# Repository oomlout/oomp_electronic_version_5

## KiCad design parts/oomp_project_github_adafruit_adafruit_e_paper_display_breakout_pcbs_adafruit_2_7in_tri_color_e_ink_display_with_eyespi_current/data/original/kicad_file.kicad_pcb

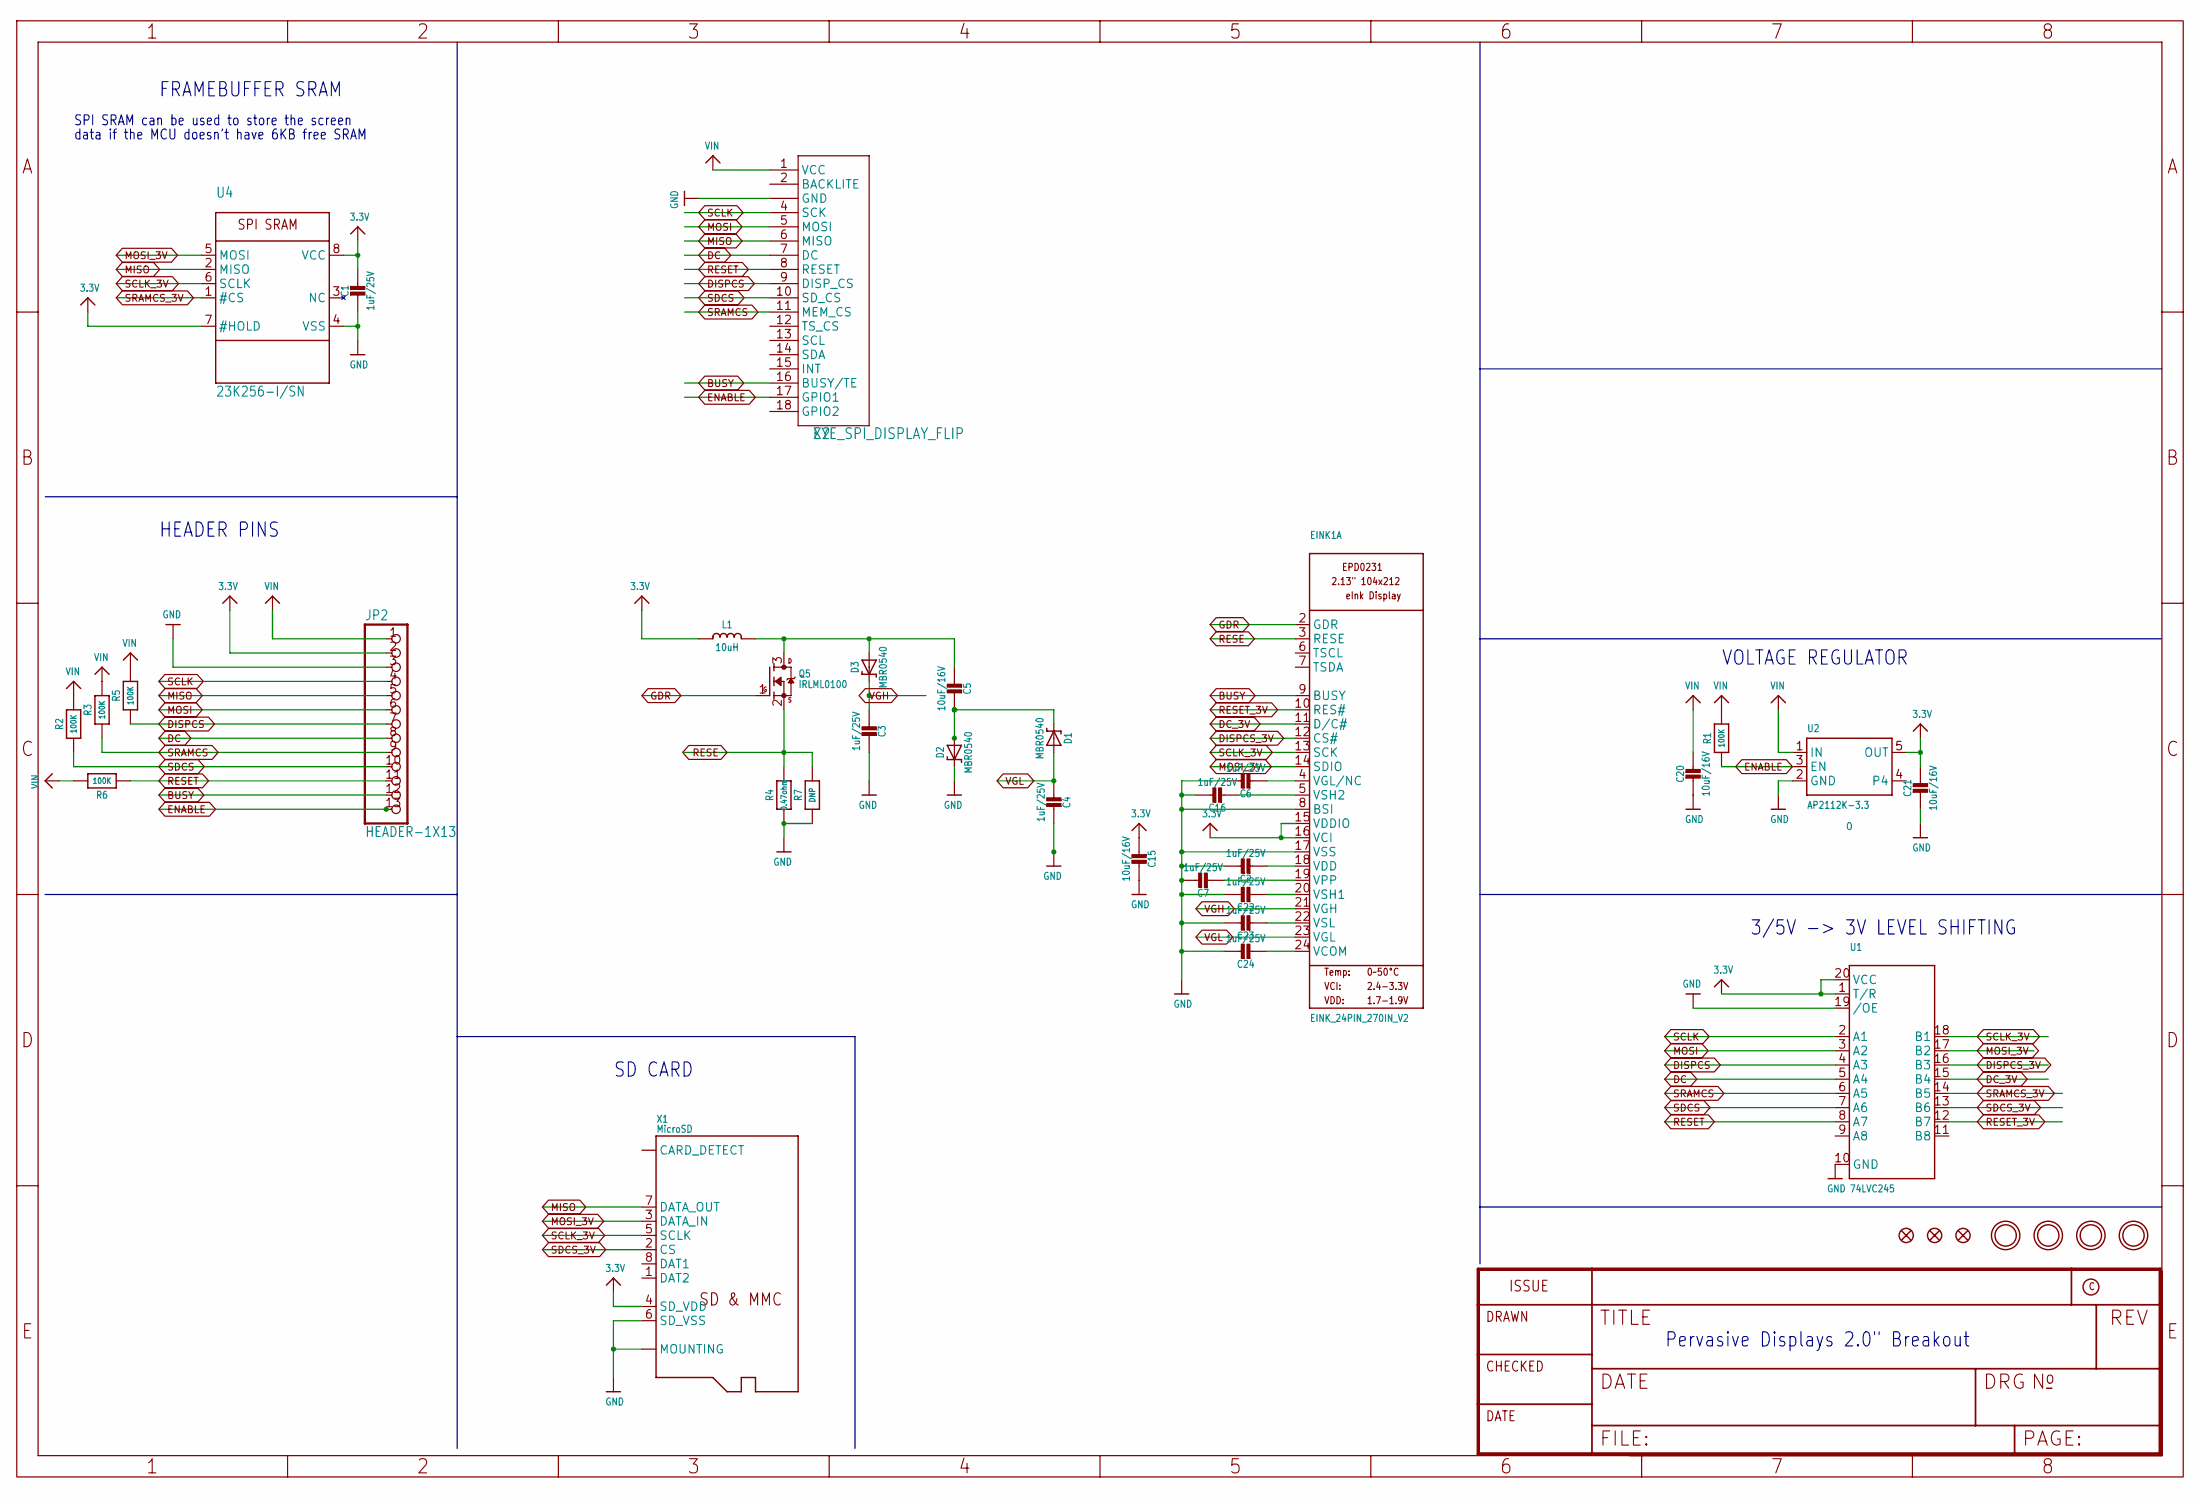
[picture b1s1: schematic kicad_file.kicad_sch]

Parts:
C1, C2, C3, C4, C6, C7, C16, C22, C23, C24: 1uF/25V; 0603-NO
C5, C15, C20, C21: 10uF/16V; 0805-NO
D1, D2, D3: MBR0540; SOD-123
EINK1: EINK_24PIN_270IN_V2; EINK_270IN_V2
FID1, FID2, FID3: FIDUCIAL_1MM
JP2: HEADER-1X13; 1X13_ROUND_70
L1: 10uH; INDUCTOR_4X4MM_NR401
Q5: IRLML0100; SOT23-WIDE
R1, R2, R3, R5, R6: 100K; 0603-NO
R4: 0.47ohm; 0603-NO
R7: DNP; 0603-NO
U1: 74LVC245; TSSOP20
U2: AP2112K-3.3; SOT23-5; JLC_ROTATION 0
U4: 23K256-I/SN; SOIC8_150MIL
U$3, U$4, U$5, U$6: MOUNTINGHOLE2.5; MOUNTINGHOLE_2.5_PLATED
X1: MicroSD; MICROSD; JLC_ROTATION 90
X2: EYE_SPI_DISPLAY_FLIP; EYE_SPI_DISPLAY_BOTCONTACT; LCSC C2856802

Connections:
3.3V: C1.1, C15.2, C21.1, EINK1.15 (VDDIO), EINK1.16 (VCI), JP2.2, L1.P$2 (2), U1.1 (T/R), U1.20 (VCC), U2.5 (OUT), U4.7 (#HOLD), U4.8 (VCC), X1.4 (SD_VDD)
BUSY: EINK1.9 (BUSY), JP2.12, X2.16 (BUSY/TE)
DC: JP2.8, U1.5 (A4), X2.7 (DC)
DC_3V: EINK1.11 (D/C#), U1.15 (B4)
DISPCS: JP2.7, R5.1, U1.4 (A3), X2.9 (DISP_CS)
DISPCS_3V: EINK1.12 (CS#), U1.16 (B3)
ENABLE: JP2.13, R1.1, U2.3 (EN), X2.17 (GPIO1)
GDR: EINK1.2 (GDR), Q5.1 (G)
GND: C1.2, C2.1, C3.2, C4.2, C6.1, C7.1, C15.1, C16.1, C20.2, C21.2, C22.1, C23.1, C24.1, D2.C, EINK1.8 (BSI), EINK1.17 (VSS), JP2.3, R4.2, R7.2, U1.10 (GND), U1.19 (/OE), U2.2 (GND), U4.4 (VSS), X1.6 (SD_VSS), X1.MT1 (MOUNTING), X1.MT2 (MOUNTING), X2.3 (GND), X2.SUPPORT1 (GND), X2.SUPPORT2 (GND)
MISO: JP2.5, U4.2 (MISO), X1.7 (DATA_OUT), X2.6 (MISO)
MOSI: JP2.6, U1.3 (A2), X2.5 (MOSI)
MOSI_3V: EINK1.14 (SDIO), U1.17 (B2), U4.5 (MOSI), X1.3 (DATA_IN)
unnamed: C7.2, EINK1.19 (VPP)
unnamed: C5.2, D1.C, D2.A
unnamed: C5.1, D3.A, L1.P$1 (1), Q5.3 (D)
unnamed: C16.2, EINK1.5 (VSH2)
unnamed: C2.2, EINK1.18 (VDD)
unnamed: C22.2, EINK1.20 (VSH1)
unnamed: C6.2, EINK1.4 (VGL/NC)
unnamed: C23.2, EINK1.22 (VSL)
unnamed: C24.2, EINK1.24 (VCOM)
RESE: EINK1.3 (RESE), Q5.2 (S), R4.1, R7.1
RESET: JP2.11, R6.1, U1.8 (A7), X2.8 (RESET)
RESET_3V: EINK1.10 (RES#), U1.12 (B7)
SCLK: JP2.4, U1.2 (A1), X2.4 (SCK)
SCLK_3V: EINK1.13 (SCK), U1.18 (B1), U4.6 (SCLK), X1.5 (SCLK)
SDCS: JP2.10, R2.1, U1.7 (A6), X2.10 (SD_CS)
SDCS_3V: U1.13 (B6), X1.2 (CS)
SRAMCS: JP2.9, R3.1, U1.6 (A5), X2.11 (MEM_CS)
SRAMCS_3V: U1.14 (B5), U4.1 (#CS)
VGH: C3.1, D3.C, EINK1.21 (VGH)
VGL: C4.1, D1.A, EINK1.23 (VGL)
VIN: C20.1, JP2.1, R1.2, R2.2, R3.2, R5.2, R6.2, U2.1 (IN), X2.1 (VCC)

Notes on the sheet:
SD CARD
Pervasive Displays 2.0" Breakout
VOLTAGE REGULATOR
3/5V -> 3V LEVEL SHIFTING
FRAMEBUFFER SRAM
data if the MCU doesn't have 6KB free SRAM
HEADER PINS
SPI SRAM can be used to store the screen

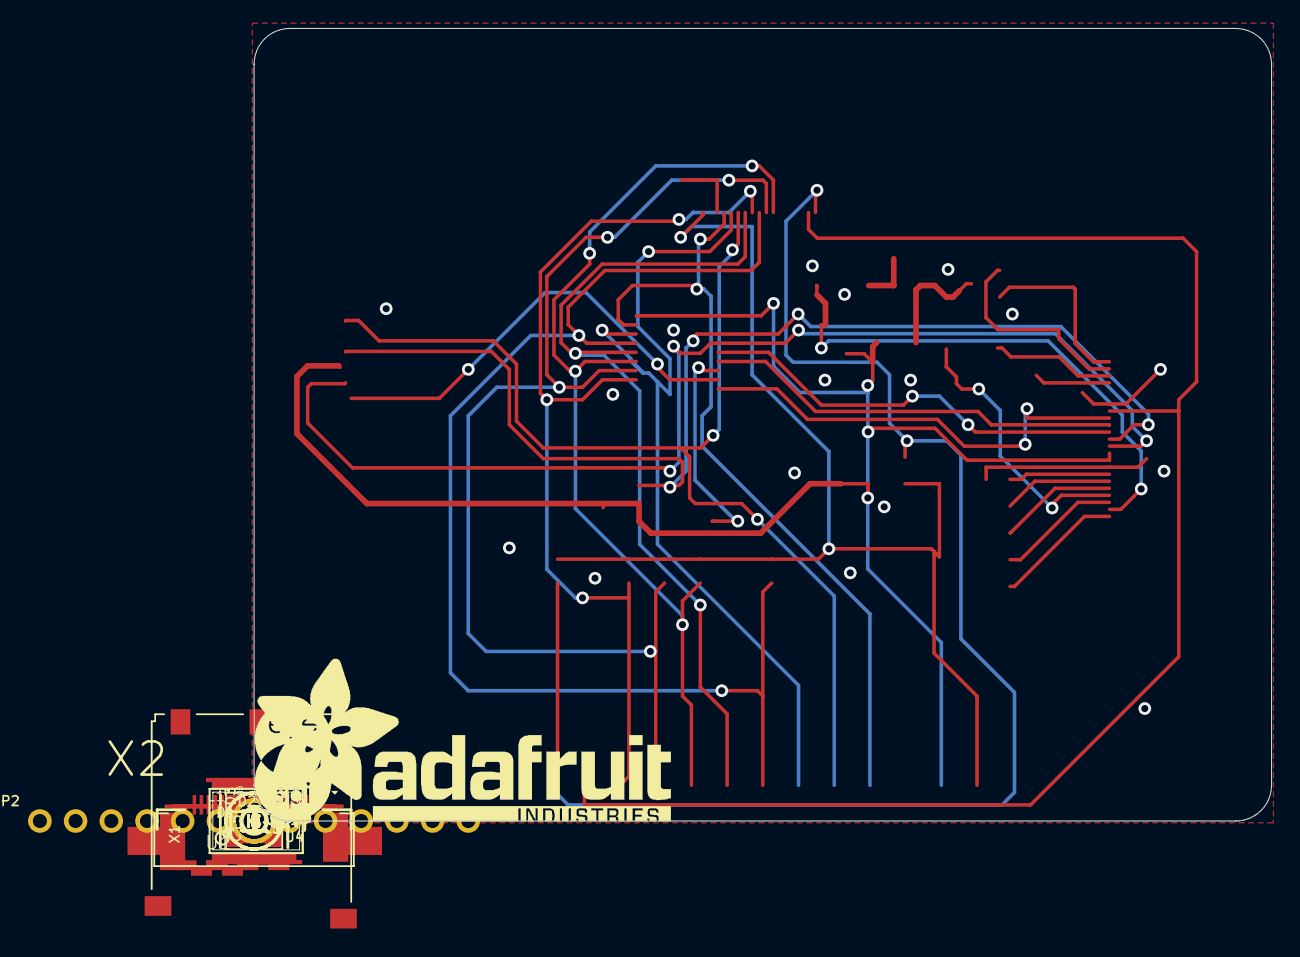
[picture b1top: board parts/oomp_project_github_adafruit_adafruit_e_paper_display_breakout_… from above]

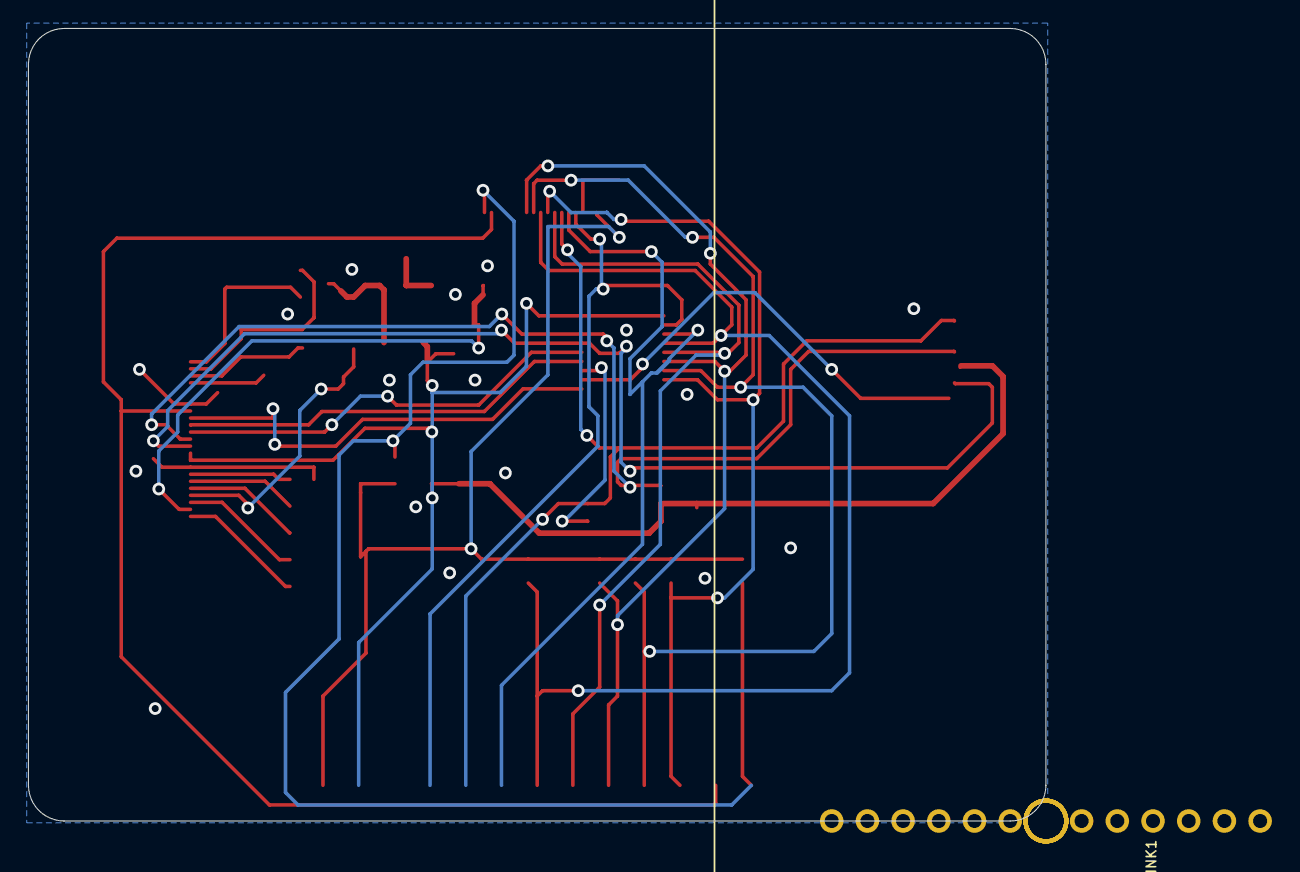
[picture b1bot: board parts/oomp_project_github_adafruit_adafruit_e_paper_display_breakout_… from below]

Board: 2 copper layers, 72.4 x 56.4 mm, 72 parts (15 on the bottom side), 33 nets.

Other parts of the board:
PLABEL0: PLABEL0
PLABEL1: PLABEL1
PLABEL2: PLABEL2
PLABEL3: PLABEL3
PLABEL4: PLABEL4
PLABEL5: PLABEL5
PLABEL6: PLABEL6
PLABEL7: PLABEL7
PLABEL8: PLABEL8
PLABEL9: PLABEL9
PLABEL10: PLABEL10
PLABEL11: PLABEL11
PLABEL12: PLABEL12
PLABEL13: PLABEL13
PLABEL14: PLABEL14
PLABEL15: PLABEL15
PLABEL16: PLABEL16
PLABEL17: PLABEL17
PLABEL18: PLABEL18
PLABEL19: PLABEL19
PLABEL20: PLABEL20
PLABEL21: PLABEL21
PLABEL22: PLABEL22
PLABEL23: PLABEL23
PLABEL24: PLABEL24
PLABEL25: PLABEL25
PLABEL26: PLABEL26
PLABEL27: PLABEL27
PLABEL28: PLABEL28
U$1: EYESPI_MINI_LOGO
U$9: PCBFEAT-REV-040
U$39: ADAFRUIT_TEXT_30MM

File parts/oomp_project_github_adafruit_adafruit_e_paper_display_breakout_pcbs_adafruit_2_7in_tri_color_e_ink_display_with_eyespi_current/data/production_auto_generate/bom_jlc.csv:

Comment,Designator,Footprint,LCSC Part #
,JP2,Adafruit 2.7in Tri-Color eInk Display with EYESPI-import-fps:1X13_ROUND_70,C2894936
,U$39,Adafruit 2.7in Tri-Color eInk Display with EYESPI-import-fps:ADAFRUIT_TEXT_30MM,
,U$1,Adafruit 2.7in Tri-Color eInk Display with EYESPI-import-fps:EYESPI_MINI_LOGO,
,U$9,Adafruit 2.7in Tri-Color eInk Display with EYESPI-import-fps:PCBFEAT-REV-040,
,PLABEL0,Adafruit 2.7in Tri-Color eInk Display with EYESPI-import-fps:PLABEL0,
,PLABEL1,Adafruit 2.7in Tri-Color eInk Display with EYESPI-import-fps:PLABEL1,
,PLABEL10,Adafruit 2.7in Tri-Color eInk Display with EYESPI-import-fps:PLABEL10,
,PLABEL11,Adafruit 2.7in Tri-Color eInk Display with EYESPI-import-fps:PLABEL11,
,PLABEL12,Adafruit 2.7in Tri-Color eInk Display with EYESPI-import-fps:PLABEL12,
,PLABEL13,Adafruit 2.7in Tri-Color eInk Display with EYESPI-import-fps:PLABEL13,
,PLABEL14,Adafruit 2.7in Tri-Color eInk Display with EYESPI-import-fps:PLABEL14,
,PLABEL15,Adafruit 2.7in Tri-Color eInk Display with EYESPI-import-fps:PLABEL15,
,PLABEL16,Adafruit 2.7in Tri-Color eInk Display with EYESPI-import-fps:PLABEL16,
,PLABEL17,Adafruit 2.7in Tri-Color eInk Display with EYESPI-import-fps:PLABEL17,
,PLABEL18,Adafruit 2.7in Tri-Color eInk Display with EYESPI-import-fps:PLABEL18,
,PLABEL19,Adafruit 2.7in Tri-Color eInk Display with EYESPI-import-fps:PLABEL19,
,PLABEL2,Adafruit 2.7in Tri-Color eInk Display with EYESPI-import-fps:PLABEL2,
,PLABEL20,Adafruit 2.7in Tri-Color eInk Display with EYESPI-import-fps:PLABEL20,
,PLABEL21,Adafruit 2.7in Tri-Color eInk Display with EYESPI-import-fps:PLABEL21,
,PLABEL22,Adafruit 2.7in Tri-Color eInk Display with EYESPI-import-fps:PLABEL22,
,PLABEL23,Adafruit 2.7in Tri-Color eInk Display with EYESPI-import-fps:PLABEL23,
,PLABEL24,Adafruit 2.7in Tri-Color eInk Display with EYESPI-import-fps:PLABEL24,
,PLABEL25,Adafruit 2.7in Tri-Color eInk Display with EYESPI-import-fps:PLABEL25,
,PLABEL26,Adafruit 2.7in Tri-Color eInk Display with EYESPI-import-fps:PLABEL26,
,PLABEL27,Adafruit 2.7in Tri-Color eInk Display with EYESPI-import-fps:PLABEL27,
,PLABEL28,Adafruit 2.7in Tri-Color eInk Display with EYESPI-import-fps:PLABEL28,
,PLABEL3,Adafruit 2.7in Tri-Color eInk Display with EYESPI-import-fps:PLABEL3,
,PLABEL4,Adafruit 2.7in Tri-Color eInk Display with EYESPI-import-fps:PLABEL4,
,PLABEL5,Adafruit 2.7in Tri-Color eInk Display with EYESPI-import-fps:PLABEL5,
,PLABEL6,Adafruit 2.7in Tri-Color eInk Display with EYESPI-import-fps:PLABEL6,
,PLABEL7,Adafruit 2.7in Tri-Color eInk Display with EYESPI-import-fps:PLABEL7,
,PLABEL8,Adafruit 2.7in Tri-Color eInk Display with EYESPI-import-fps:PLABEL8,
,PLABEL9,Adafruit 2.7in Tri-Color eInk Display with EYESPI-import-fps:PLABEL9,
0.47ohm,R4,Adafruit 2.7in Tri-Color eInk Display with EYESPI-import-fps:0603-NO,
100K,"R1,R2,R3,R5,R6",Adafruit 2.7in Tri-Color eInk Display with EYESPI-import-fps:0603-NO,C25803
10uF/16V,"C5,C15,C20,C21",Adafruit 2.7in Tri-Color eInk Display with EYESPI-import-fps:0805-NO,
10uH,L1,Adafruit 2.7in Tri-Color eInk Display with EYESPI-import-fps:INDUCTOR_4X4MM_NR401,
1uF/25V,"C1,C2,C3,C4,C6,C7,C16,C22,C23,C24",Adafruit 2.7in Tri-Color eInk Display with EYESPI-import-fps:0603-NO,C5673
23K256-I/SN,U4,Adafruit 2.7in Tri-Color eInk Display with EYESPI-import-fps:SOIC8_150MIL,
74LVC245,U1,Adafruit 2.7in Tri-Color eInk Display with EYESPI-import-fps:TSSOP20,
AP2112K-3.3,U2,Adafruit 2.7in Tri-Color eInk Display with EYESPI-import-fps:SOT23-5,
DNP,R7,Adafruit 2.7in Tri-Color eInk Display with EYESPI-import-fps:0603-NO,
EINK_24PIN_270IN_V2,EINK1,Adafruit 2.7in Tri-Color eInk Display with EYESPI-import-fps:EINK_270IN_V2,
EYE_SPI_DISPLAY_FLIP,X2,Adafruit 2.7in Tri-Color eInk Display with EYESPI-import-fps:EYE_SPI_DISPLAY_BOTCONTACT,
IRLML0100,Q5,Adafruit 2.7in Tri-Color eInk Display with EYESPI-import-fps:SOT23-WIDE,
MBR0540,"D1,D2,D3",Adafruit 2.7in Tri-Color eInk Display with EYESPI-import-fps:SOD-123,
MicroSD,X1,Adafruit 2.7in Tri-Color eInk Display with EYESPI-import-fps:MICROSD,

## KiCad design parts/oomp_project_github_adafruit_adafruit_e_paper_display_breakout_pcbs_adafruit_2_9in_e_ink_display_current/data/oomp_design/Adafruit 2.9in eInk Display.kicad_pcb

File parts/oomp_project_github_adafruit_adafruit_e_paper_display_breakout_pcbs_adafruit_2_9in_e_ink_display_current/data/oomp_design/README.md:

# OOMP KiCad design copy

Open `Adafruit 2.9in eInk Display.kicad_pro` (or the `.kicad_pcb` / `.kicad_sch`) in KiCad. Local OOMP libraries are under `libraries/`. Original inputs are preserved in [../original/](../original/).

Only verified unchanged installed KiCad defaults were renamed. Modified, custom, unmatched and unavailable items remain unchanged. Soldering variants are never swapped during conversion. Existing pad coordinates, nets and UUIDs are preserved.

See [conversion_report.yaml](conversion_report.yaml) for every conversion and skip. Copy this directory before editing; regeneration refuses to overwrite edited design files.

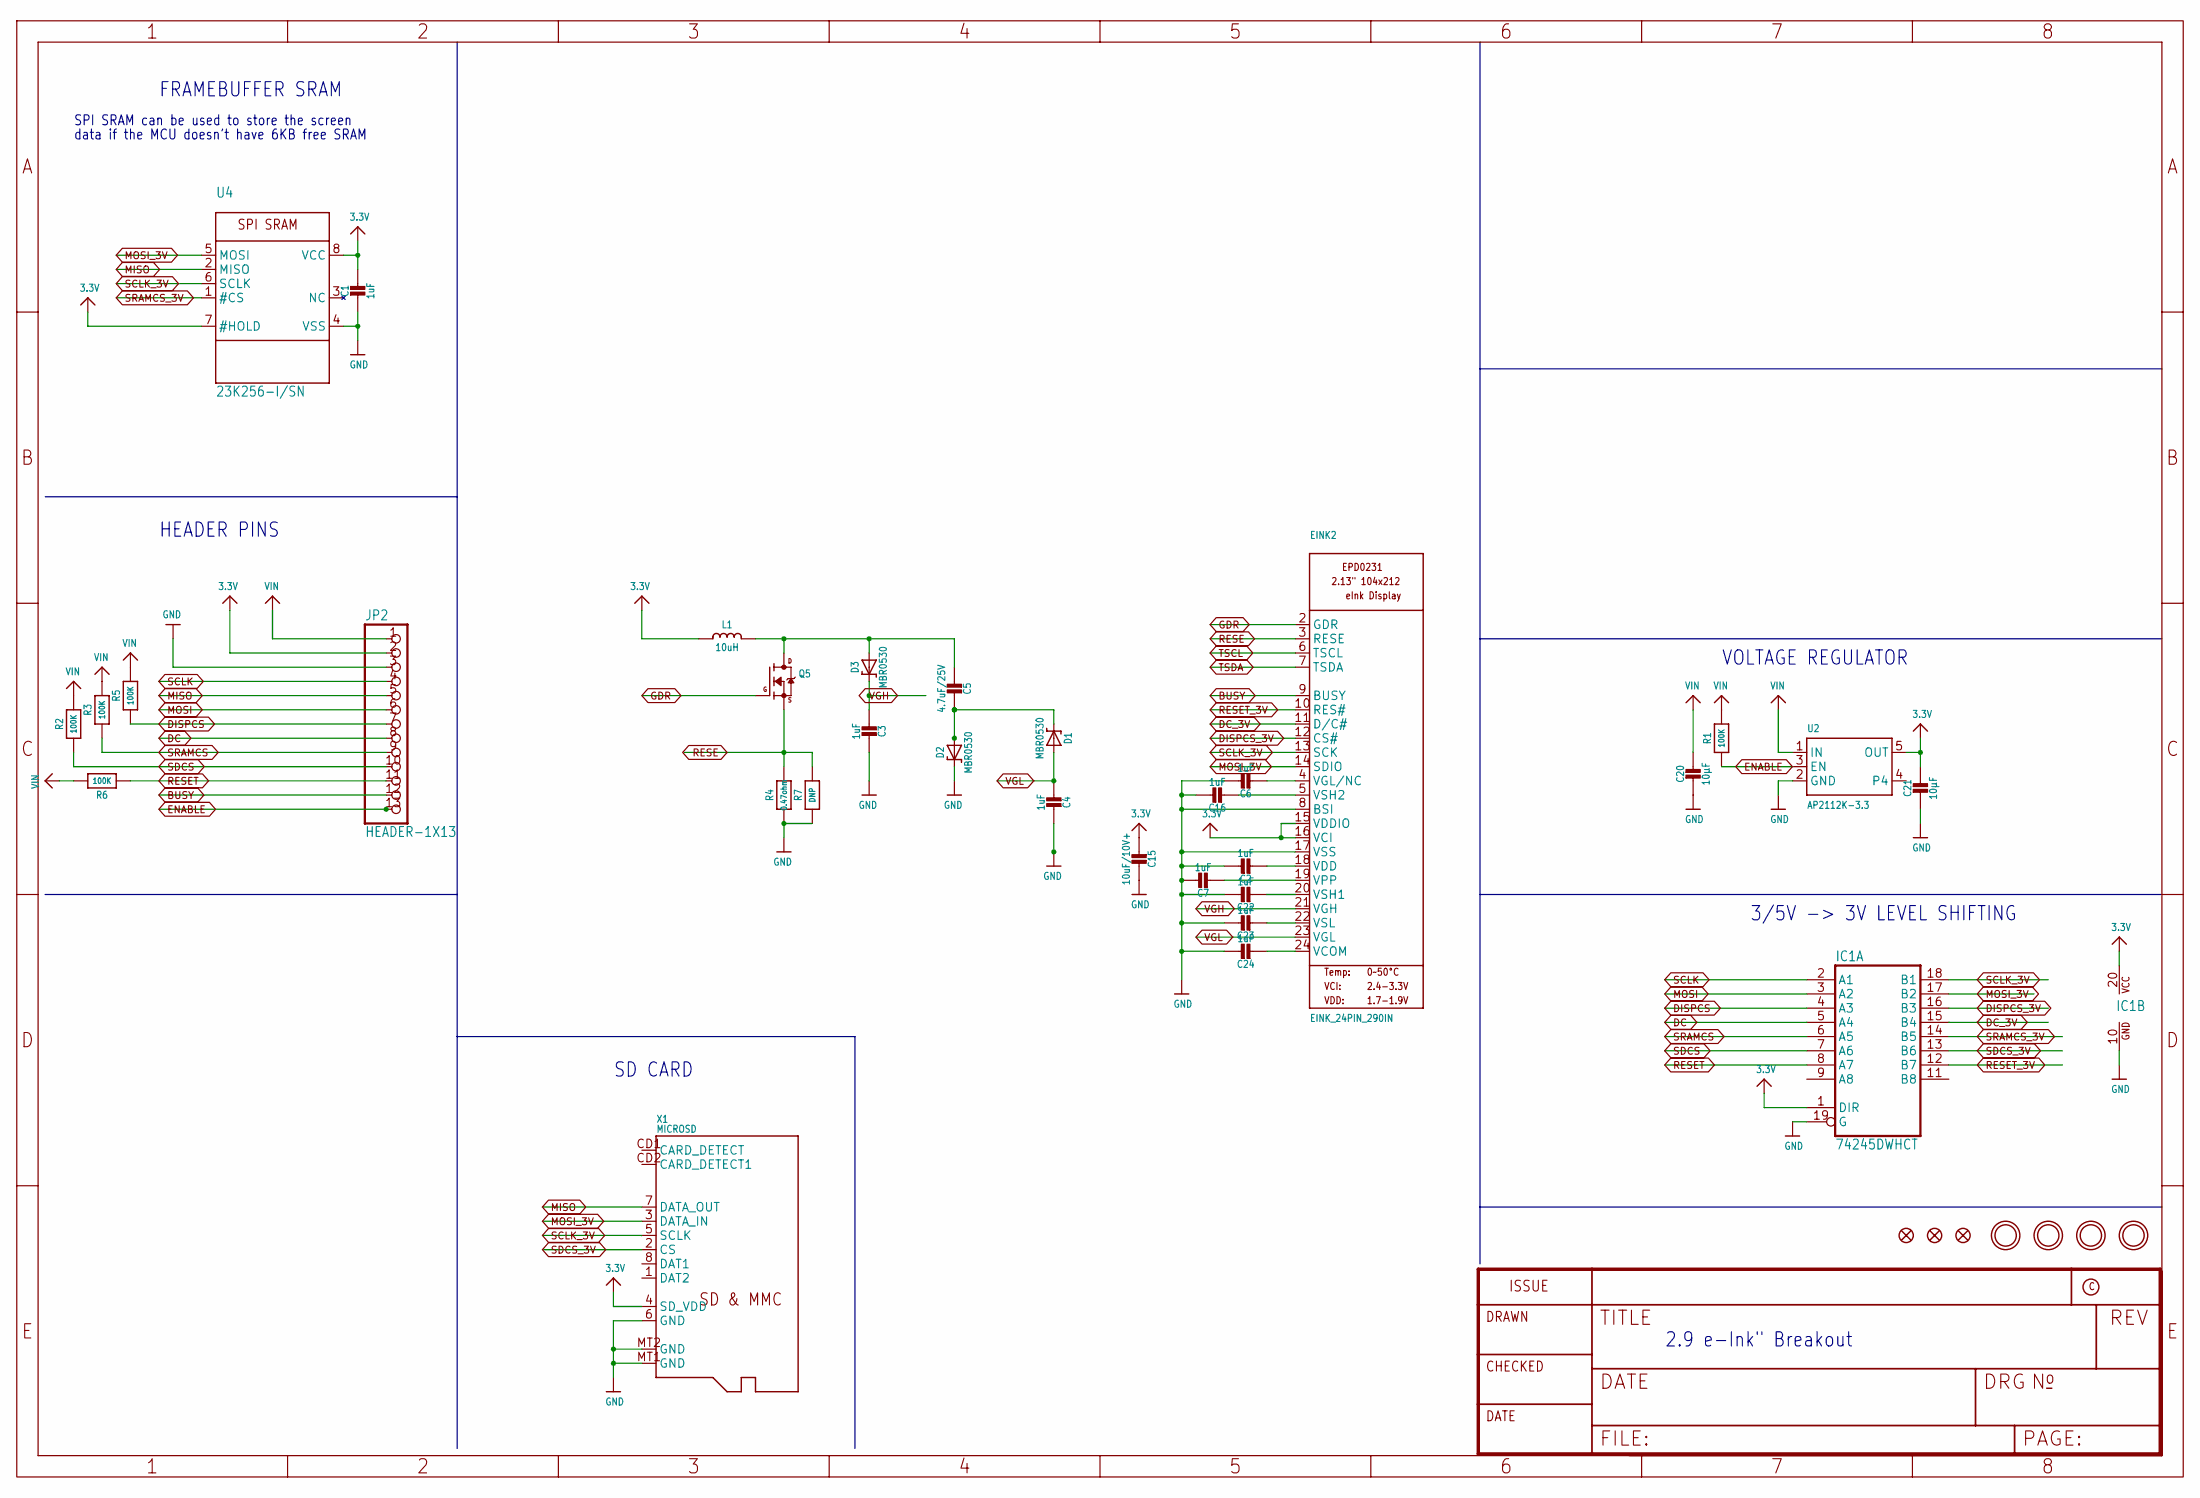
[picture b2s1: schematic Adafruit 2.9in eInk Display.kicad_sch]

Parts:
C1: 1uF; 0805_10MGAP
C2, C3, C4, C6, C7, C16, C22, C23, C24: 1uF; 0805-NO
C5: 4.7uF/25V; 0805-NO
C15: 10uF/10V+; 0805-NO
C20, C21: 10µF; 0805-NO
D1, D2, D3: MBR0530; SOD-123
EINK2: EINK_24PIN_290IN; EINK_290IN
FID1, FID2, FID3: FIDUCIAL_1MM
IC1: 74245DWHCT; SO20W
JP2: HEADER-1X13; 1X13_ROUND_70
L1: 10uH; INDUCTOR_4X4MM_NR401
Q5: IRLML0100; SOT23-3
R1, R2, R3, R5, R6: 100K; 0805-NO
R4: 0.47ohm; 0805_10MGAP
R7: DNP; 0805_10MGAP
U2: AP2112K-3.3; SOT23-5
U4: 23K256-I/SN; SOIC8_150MIL
U$3, U$4, U$5, U$6: MOUNTINGHOLE2.5; MOUNTINGHOLE_2.5_PLATED
X1: MICROSD

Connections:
3.3V: C1.1, C15.2, C21.1, EINK2.15 (VDDIO), EINK2.16 (VCI), IC1.1 (DIR), IC1.20 (VCC), JP2.2, L1.P$2 (2), U2.5 (OUT), U4.7 (#HOLD), U4.8 (VCC), X1.4 (SD_VDD)
BUSY: EINK2.9 (BUSY), JP2.12
DC: IC1.5 (A4), JP2.8
DC_3V: EINK2.11 (D/C#), IC1.15 (B4)
DISPCS: IC1.4 (A3), JP2.7, R5.1
DISPCS_3V: EINK2.12 (CS#), IC1.16 (B3)
ENABLE: JP2.13, R1.1, U2.3 (EN)
GDR: EINK2.2 (GDR), Q5.1 (G)
GND: C1.2, C2.1, C3.2, C4.2, C6.1, C7.1, C15.1, C16.1, C20.2, C21.2, C22.1, C23.1, C24.1, D2.C, EINK2.8 (BSI), EINK2.17 (VSS), IC1.10 (GND), IC1.19 (G), JP2.3, R4.2, R7.2, U2.2 (GND), U4.4 (VSS), X1.6 (GND), X1.MT1 (GND), X1.MT2 (GND)
MISO: JP2.5, U4.2 (MISO), X1.7 (DATA_OUT)
MOSI: IC1.3 (A2), JP2.6
MOSI_3V: EINK2.14 (SDIO), IC1.17 (B2), U4.5 (MOSI), X1.3 (DATA_IN)
unnamed: C7.2, EINK2.19 (VPP)
unnamed: C5.2, D1.C, D2.A
unnamed: C5.1, D3.A, L1.P$1 (1), Q5.3 (D)
unnamed: C16.2, EINK2.5 (VSH2)
unnamed: C2.2, EINK2.18 (VDD)
unnamed: C22.2, EINK2.20 (VSH1)
unnamed: C6.2, EINK2.4 (VGL/NC)
unnamed: C23.2, EINK2.22 (VSL)
unnamed: C24.2, EINK2.24 (VCOM)
RESE: EINK2.3 (RESE), Q5.2 (S), R4.1, R7.1
RESET: IC1.8 (A7), JP2.11, R6.1
RESET_3V: EINK2.10 (RES#), IC1.12 (B7)
SCLK: IC1.2 (A1), JP2.4
SCLK_3V: EINK2.13 (SCK), IC1.18 (B1), U4.6 (SCLK), X1.5 (SCLK)
SDCS: IC1.7 (A6), JP2.10, R2.1
SDCS_3V: IC1.13 (B6), X1.2 (CS)
SRAMCS: IC1.6 (A5), JP2.9, R3.1
SRAMCS_3V: IC1.14 (B5), U4.1 (#CS)
TSCL: EINK2.6 (TSCL)
TSDA: EINK2.7 (TSDA)
VGH: C3.1, D3.C, EINK2.21 (VGH)
VGL: C4.1, D1.A, EINK2.23 (VGL)
VIN: C20.1, JP2.1, R1.2, R2.2, R3.2, R5.2, R6.2, U2.1 (IN)

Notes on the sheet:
3/5V -> 3V LEVEL SHIFTING
VOLTAGE REGULATOR
2.9 e-Ink" Breakout
FRAMEBUFFER SRAM
SPI SRAM can be used to store the screen
SD CARD
HEADER PINS
data if the MCU doesn't have 6KB free SRAM

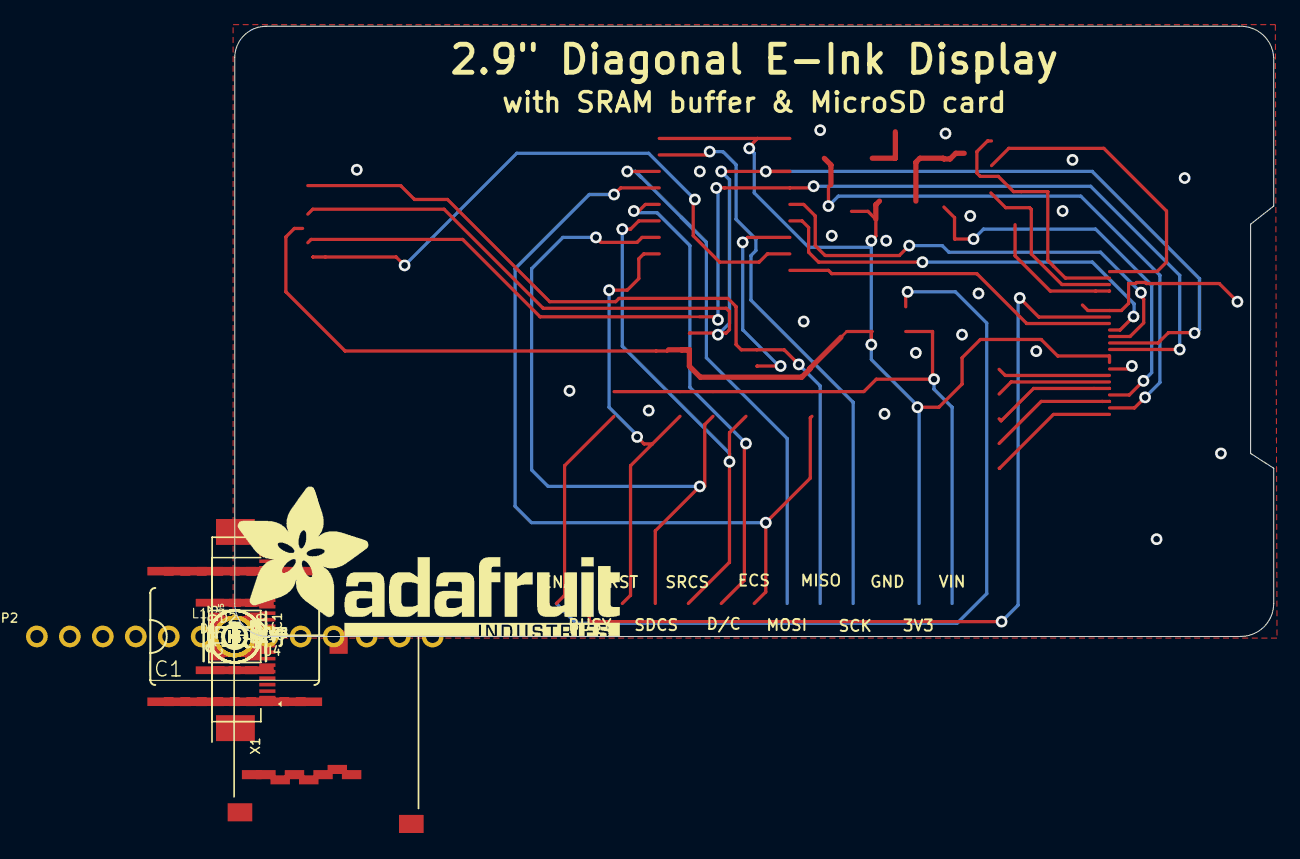
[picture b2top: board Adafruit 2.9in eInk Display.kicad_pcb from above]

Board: 2 copper layers, 80.0 x 47.0 mm, 41 parts (1 on the bottom side), 33 nets.

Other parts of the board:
U$9: PCBFEAT-REV-040
U$39: ADAFRUIT_TEXT_30MM

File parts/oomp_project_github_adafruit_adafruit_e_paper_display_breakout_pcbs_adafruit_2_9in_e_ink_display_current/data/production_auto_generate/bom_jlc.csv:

Comment,Designator,Footprint,LCSC Part #
,JP2,Adafruit 2.9in eInk Display-import-fps:1X13_ROUND_70,C2894936
,U$39,Adafruit 2.9in eInk Display-import-fps:ADAFRUIT_TEXT_30MM,
,U$9,Adafruit 2.9in eInk Display-import-fps:PCBFEAT-REV-040,
0.47ohm,R4,Adafruit 2.9in eInk Display-import-fps:0805_10MGAP,
100K,"R1,R2,R3,R5,R6",Adafruit 2.9in eInk Display-import-fps:0805-NO,C149504
10uF/10V+,C15,Adafruit 2.9in eInk Display-import-fps:0805-NO,
10uH,L1,Adafruit 2.9in eInk Display-import-fps:INDUCTOR_4X4MM_NR401,
10µF,"C20,C21",Adafruit 2.9in eInk Display-import-fps:0805-NO,
1uF,"C2,C3,C4,C6,C7,C16,C22,C23,C24",Adafruit 2.9in eInk Display-import-fps:0805-NO,
1uF,C1,Adafruit 2.9in eInk Display-import-fps:0805_10MGAP,
23K256-I/SN,U4,Adafruit 2.9in eInk Display-import-fps:SOIC8_150MIL,
4.7uF/25V,C5,Adafruit 2.9in eInk Display-import-fps:0805-NO,
74HCT245DW,IC1,Adafruit 2.9in eInk Display-import-fps:SO20W,
AP2112K-3.3,U2,Adafruit 2.9in eInk Display-import-fps:SOT23-5,
DNP,R7,Adafruit 2.9in eInk Display-import-fps:0805_10MGAP,
EINK_24PIN_290IN,EINK2,Adafruit 2.9in eInk Display-import-fps:EINK_290IN,
IRLML0100,Q5,Adafruit 2.9in eInk Display-import-fps:SOT23-3,
MBR0530,"D1,D2,D3",Adafruit 2.9in eInk Display-import-fps:SOD-123,
MICROSD,X1,Adafruit 2.9in eInk Display-import-fps:MICROSD,

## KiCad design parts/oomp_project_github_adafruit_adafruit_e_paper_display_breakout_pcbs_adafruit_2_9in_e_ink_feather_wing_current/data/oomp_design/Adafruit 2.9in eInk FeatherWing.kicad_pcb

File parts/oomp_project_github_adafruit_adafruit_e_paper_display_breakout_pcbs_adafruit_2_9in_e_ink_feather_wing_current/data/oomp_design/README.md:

# OOMP KiCad design copy

Open `Adafruit 2.9in eInk FeatherWing.kicad_pro` (or the `.kicad_pcb` / `.kicad_sch`) in KiCad. Local OOMP libraries are under `libraries/`. Original inputs are preserved in [../original/](../original/).

Only verified unchanged installed KiCad defaults were renamed. Modified, custom, unmatched and unavailable items remain unchanged. Soldering variants are never swapped during conversion. Existing pad coordinates, nets and UUIDs are preserved.

See [conversion_report.yaml](conversion_report.yaml) for every conversion and skip. Copy this directory before editing; regeneration refuses to overwrite edited design files.

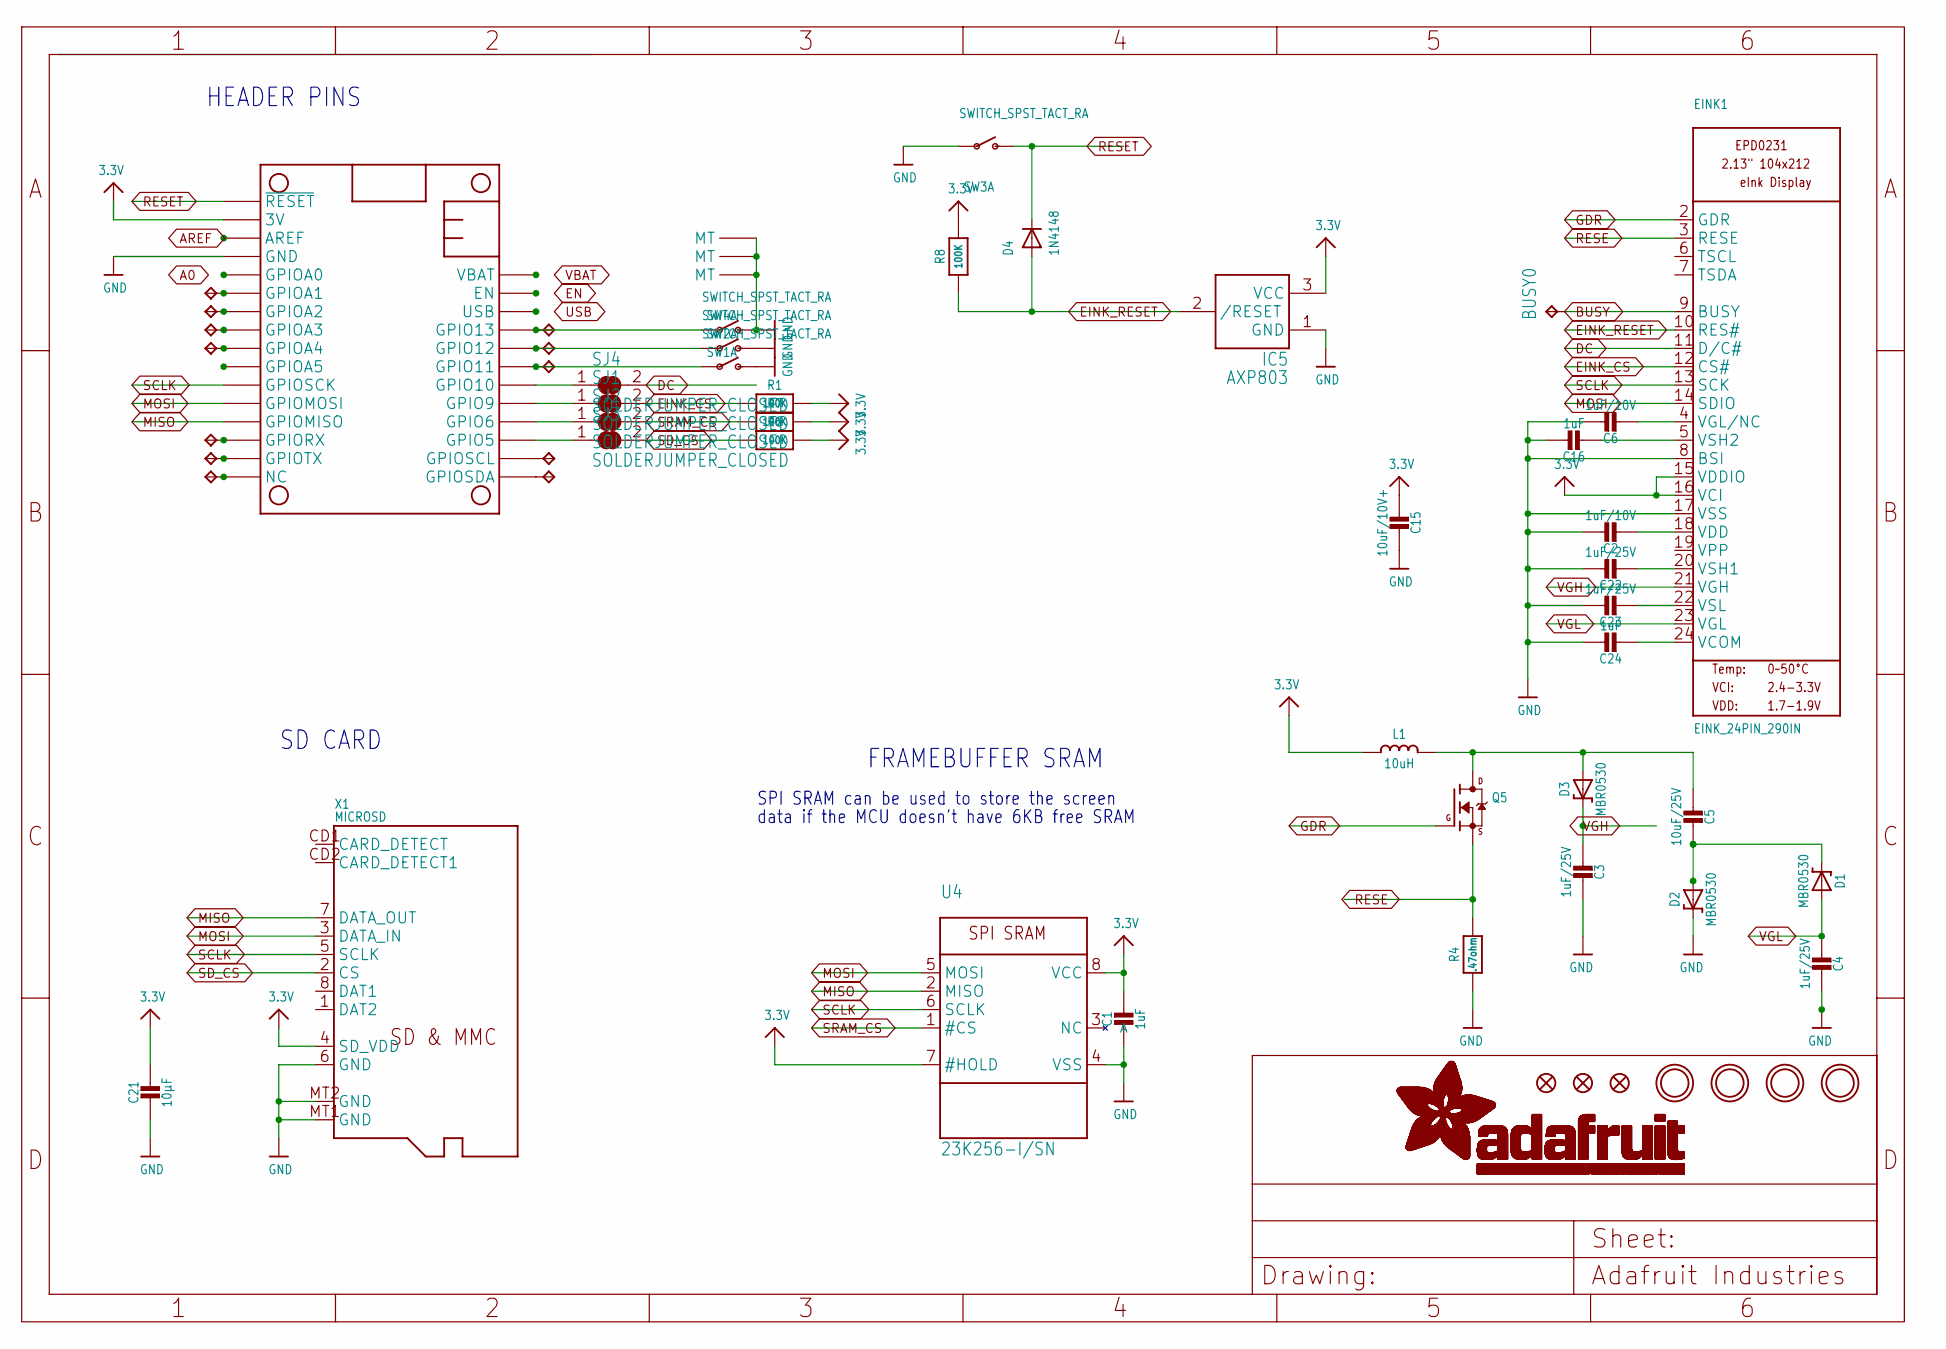
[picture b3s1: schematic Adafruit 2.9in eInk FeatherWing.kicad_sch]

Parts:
BUSY0: TPTP15SQ; TP15SQ
C1: 1uF; 0805_10MGAP
C2, C6: 1uF/10V; 0805-NO
C3, C4, C22, C23: 1uF/25V; 0805-NO
C5: 10uF/25V; 0805-NO
C15: 10uF/10V+; 0805-NO
C16, C24: 1uF; 0805-NO
C21: 10µF; 0805-NO
D1, D2, D3: MBR0530; SOD-123
D4: 1N4148; SOD-323F
EINK1: EINK_24PIN_290IN; EINK_290IN
FID1, FID2, FID3: FIDUCIAL_1MM
IC5: AXP803; SOT23
L1: 10uH; INDUCTOR_4X4MM_NR401
MS1: FEATHERWING_SMTDUALNOHOLES; FEATHERWING_SMT_NOHOLES
Q5: IRLML0100; SOT23-3
R1, R6, R7, R8: 100K; 0603-NO
R4: .47ohm; 0805_10MGAP
SJ1, SJ2, SJ3, SJ4: SOLDERJUMPER_CLOSED; SOLDERJUMPER_CLOSEDWIRE
SW1, SW2, SW3, SW4: SWITCH_SPST_TACT_RA; SPST_TACTILE_RA
TP1, TP2, TP3, TP4, TP5, TP6, TP7, TP8, TP9, TP11, TP12, TP13: TPTP15SQ; TP15SQ
U4: 23K256-I/SN; SOIC8_150MIL
U$3, U$4, U$5, U$6: MOUNTINGHOLE2.5; MOUNTINGHOLE_2.5_PLATED
X1: MICROSD

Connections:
3.3V: C1.1, C15.2, C21.1, EINK1.15 (VDDIO), EINK1.16 (VCI), IC5.3 (VCC), L1.P$2 (2), MS1.2 (3V), MS1.2B (3V), R1.2, R6.2, R7.2, R8.2, U4.7 (#HOLD), U4.8 (VCC), X1.4 (SD_VDD)
A0: MS1.5 (GPIOA0), MS1.5B (GPIOA0)
AREF: MS1.3 (AREF), MS1.3B (AREF)
BUSY: BUSY0.TP, EINK1.9 (BUSY)
DC: EINK1.11 (D/C#), SJ4.2
EINK_CS: EINK1.12 (CS#), R1.1, SJ1.2
EINK_RESET: D4.A, EINK1.10 (RES#), IC5.2 (/RESET), R8.1
EN: MS1.27 (EN), MS1.27B (EN)
GDR: EINK1.2 (GDR), Q5.1 (G)
GND: C1.2, C2.1, C3.2, C4.2, C6.1, C15.1, C16.1, C21.2, C22.1, C23.1, C24.1, D2.C, EINK1.8 (BSI), EINK1.17 (VSS), IC5.1 (GND), MS1.4 (GND), MS1.4B (GND), R4.2, SW1.2 (S), SW1.MT1 (MT), SW1.MT2 (MT), SW2.2 (S), SW2.MT1 (MT), SW2.MT2 (MT), SW3.1, SW4.2 (S), SW4.MT1 (MT), SW4.MT2 (MT), U4.4 (VSS), X1.6 (GND), X1.MT1 (GND), X1.MT2 (GND)
H: MS1.19 (GPIO5), MS1.19B (GPIO5), SJ3.1
I: MS1.20 (GPIO6), MS1.20B (GPIO6), SJ2.1
J: MS1.21 (GPIO9), MS1.21B (GPIO9), SJ1.1
K: MS1.22 (GPIO10), MS1.22B (GPIO10), SJ4.1
MISO: MS1.13 (GPIOMISO), MS1.13B (GPIOMISO), U4.2 (MISO), X1.7 (DATA_OUT)
MOSI: EINK1.14 (SDIO), MS1.12 (GPIOMOSI), MS1.12B (GPIOMOSI), U4.5 (MOSI), X1.3 (DATA_IN)
unnamed: MS1.10 (GPIOA5), MS1.10B (GPIOA5)
unnamed: C5.2, D1.C, D2.A
unnamed: C5.1, D3.A, L1.P$1 (1), Q5.3 (D)
unnamed: C16.2, EINK1.5 (VSH2)
unnamed: C2.2, EINK1.18 (VDD)
unnamed: C22.2, EINK1.20 (VSH1)
unnamed: MS1.6 (GPIOA1), MS1.6B (GPIOA1), TP6.TP
unnamed: C6.2, EINK1.4 (VGL/NC)
unnamed: MS1.7 (GPIOA2), MS1.7B (GPIOA2), TP7.TP
unnamed: MS1.8 (GPIOA3), MS1.8B (GPIOA3), TP8.TP
unnamed: MS1.9 (GPIOA4), MS1.9B (GPIOA4), TP9.TP
unnamed: MS1.14 (GPIORX), MS1.14B (GPIORX), TP11.TP
unnamed: MS1.15 (GPIOTX), MS1.15B (GPIOTX), TP12.TP
unnamed: MS1.16 (NC), MS1.16B (NC), TP13.TP
unnamed: MS1.17 (GPIOSDA), MS1.17B (GPIOSDA), TP4.TP
unnamed: MS1.18 (GPIOSCL), MS1.18B (GPIOSCL), TP3.TP
unnamed: MS1.23 (GPIO11), MS1.23B (GPIO11), SW1.1, TP1.TP
unnamed: MS1.24 (GPIO12), MS1.24B (GPIO12), SW2.1, TP2.TP
unnamed: MS1.25 (GPIO13), MS1.25B (GPIO13), SW4.1, TP5.TP
unnamed: C23.2, EINK1.22 (VSL)
unnamed: C24.2, EINK1.24 (VCOM)
RESE: EINK1.3 (RESE), Q5.2 (S), R4.1
RESET: D4.C, MS1.1 (~RESET), MS1.1B (~RESET), SW3.2 (S)
SCLK: EINK1.13 (SCK), MS1.11 (GPIOSCK), MS1.11B (GPIOSCK), U4.6 (SCLK), X1.5 (SCLK)
SD_CS: R6.1, SJ3.2, X1.2 (CS)
SRAM_CS: R7.1, SJ2.2, U4.1 (#CS)
USB: MS1.26 (USB), MS1.26B (USB)
VBAT: MS1.28 (VBAT), MS1.28B (VBAT)
VGH: C3.1, D3.C, EINK1.21 (VGH)
VGL: C4.1, D1.A, EINK1.23 (VGL)

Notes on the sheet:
FRAMEBUFFER SRAM
data if the MCU doesn't have 6KB free SRAM
HEADER PINS
SPI SRAM can be used to store the screen
SD CARD
